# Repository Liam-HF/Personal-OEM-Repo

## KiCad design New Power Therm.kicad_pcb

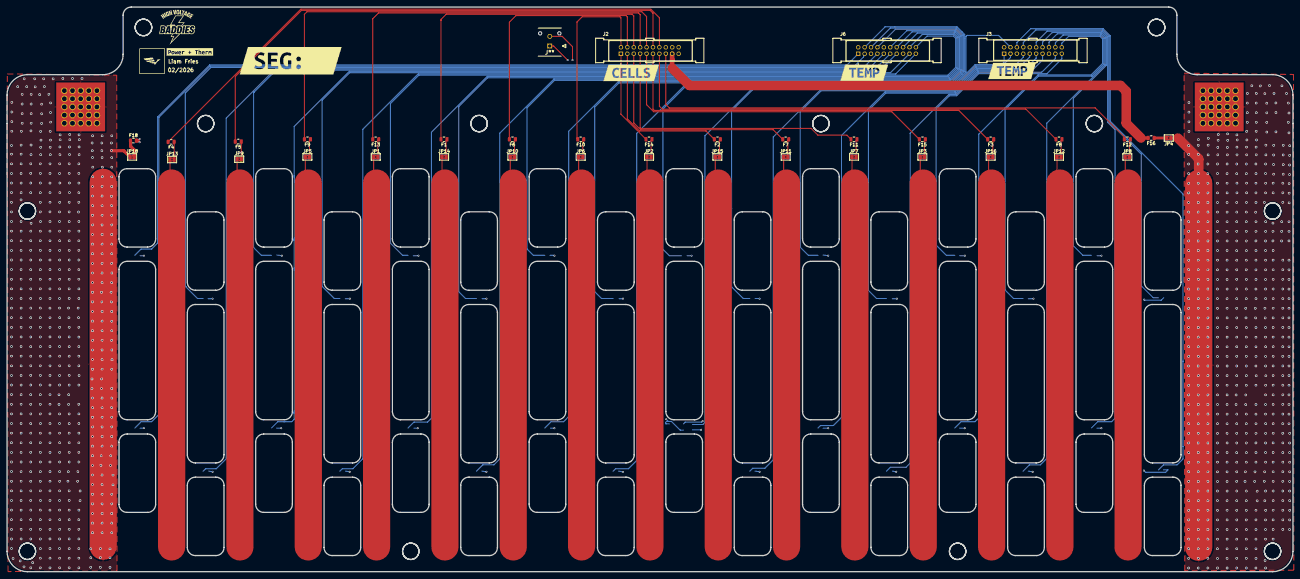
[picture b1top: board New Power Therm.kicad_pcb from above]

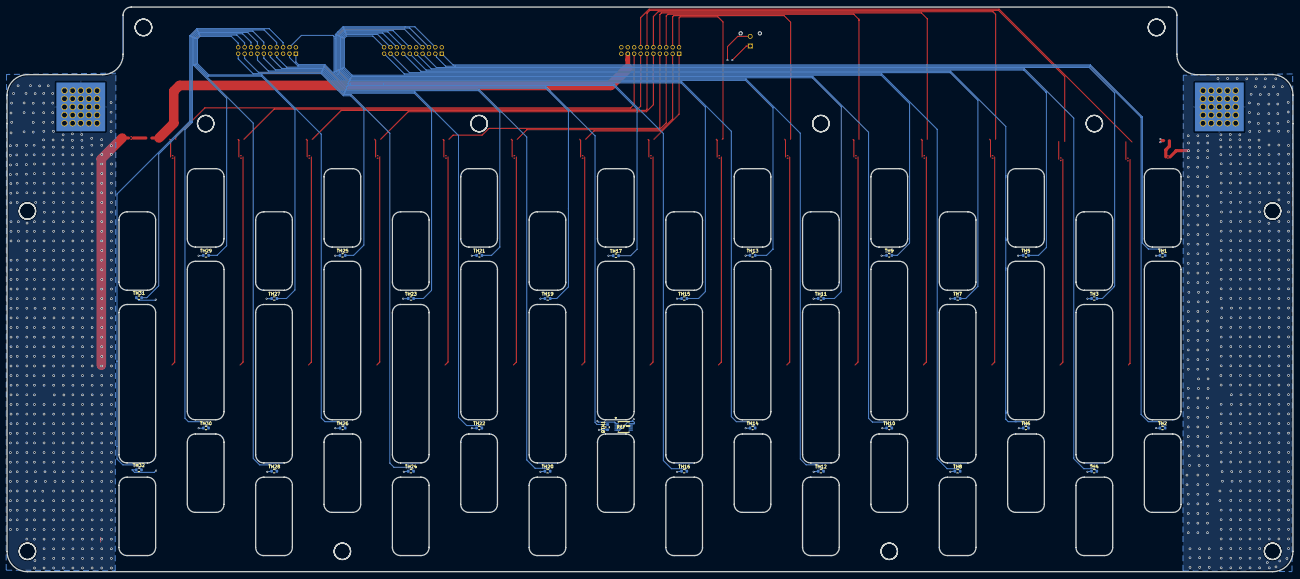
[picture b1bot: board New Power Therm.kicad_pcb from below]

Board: 4 copper layers, 401.0 x 176.1 mm, 92 parts (32 on the bottom side), 66 nets.

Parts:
F1, F2, F3, F4, F5, F6, F7, F8, F9, F10, F11, F12, F13, F14, F15, F16, F18: 200mA_Fuse; Fuse_0805_2012Metric
J2: J_Bond_Pad_4p
J2#2, J3, J6: EHT-110-01-F-D; SAMTEC_EHT-110-01-X-D (J_EHT-110-01-F-D)
J5, J6#2, J7, J8, J9, J10, J11, J12, J13, J14, J15, J16, J17, J18, J19, J20: Battery Cell Spot Weld; J_Bond_Pad_4p
J**: 43045-02YY_121314; J_Molex_Header_01x02_VT - 43045-02YY_121314
JP1, JP2, JP3, JP4, JP5, JP6, JP7, JP8, JP9, JP10, JP11, JP12, JP13, JP14, JP15, JP16, JP18: SolderJumper_2_Bridged; SolderJumper-2_P1.3mm_Bridged2Bar_Pad1.0x1.5mm
TH1, TH2, TH3, TH4, TH5, TH6, TH7, TH8, TH9, TH10, TH11, TH12, TH13, TH14, TH15, TH16, TH17, TH18, TH19, TH20, TH21, TH22, TH23, TH24, TH25, TH26, TH27, TH28, TH29, TH30, TH31, TH32: Thermistor; R_0603_1608Metric
kibuzzard-6738FA22: G***; kibuzzard-6738FA22
kibuzzard-6738FB72, kibuzzard-6738FB72#2: G***; kibuzzard-6738FB72
kibuzzard-6739182D: G***; kibuzzard-6739182D
kibuzzard-67390047: G***; kibuzzard-67390047

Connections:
/Cells[1:16]/CELL0: J20.1, JP18.1 (A)
CELL1: F4.2, J2#2.14, J5.1, JP13.1 (A)
CELL2: F5.2, J2#2.12, J6#2.1, JP9.1 (A)
CELL3: F9.2, J2#2.10, J8.1, JP5.1 (A)
CELL4: F13.2, J2#2.08, J9.1, JP1.1 (A)
CELL5: F1.2, J2#2.06, J10.1, JP14.1 (A)
CELL6: F6.2, J2#2.04, J11.1, JP10.1 (A)
CELL7: F10.2, J2#2.02, J12.1, JP6.1 (A)
CELL8: F14.2, J2#2.01, J13.1, JP2.1 (A)
CELL9: F2.2, J2#2.03, J14.1, JP15.1 (A)
CELL10: F7.2, J2#2.05, J15.1, JP11.1 (A)
CELL11: F11.2, J2#2.07, J16.1, JP7.1 (A)
CELL12: F15.2, J2#2.09, J17.1, JP3.1 (A)
CELL13: F3.2, J2#2.11, J18.1, JP16.1 (A)
CELL14: F8.2, J2#2.13, J19.1, JP12.1 (A)
CELL15: F12.2, J2#2.15, J7.1, JP8.1 (A)
CELL16: F16.2, J2.1, J2#2.17, JP4.1 (A)
GND: F18.2, J2#2.16, J2#2.18, J2#2.19, J2#2.20, J3.05, J3.10, J3.15, J6.05, J6.10, J6.15, TH1.1, TH2.1, TH3.1, TH4.1, TH5.1, TH6.1, TH7.1, TH8.1, TH9.1, TH10.1, TH11.1, TH12.1, TH13.1, TH14.1, TH15.1, TH16.1, TH17.1, TH18.1, TH19.1, TH20.1, TH21.1, TH22.1, TH23.1, TH24.1, TH25.1, TH26.1, TH27.1, TH28.1, TH29.1, TH30.1, TH31.1, TH32.1
unnamed: F5.1, F13.1, JP1.2 (B), JP9.2 (B)
unnamed: F14.1, JP2.2 (B)
unnamed: F15.1, JP3.2 (B)
unnamed: F16.1, JP4.2 (B)
unnamed: F9.1, JP5.2 (B)
unnamed: F10.1, JP6.2 (B)
unnamed: F11.1, JP7.2 (B)
unnamed: F12.1, JP8.2 (B)
unnamed: F6.1, JP10.2 (B)
unnamed: F7.1, JP11.2 (B)
unnamed: F8.1, JP12.2 (B)
unnamed: F4.1, JP13.2 (B)
unnamed: F1.1, JP14.2 (B)
unnamed: F2.1, JP15.2 (B)
unnamed: F3.1, JP16.2 (B)
unnamed: F18.1, JP18.2 (B)
Therm1: J6.01, TH1.2
Therm2: J6.03, TH2.2
Therm3: J6.07, TH3.2
Therm4: J6.09, TH4.2
Therm5: J6.11, TH5.2
Therm6: J6.13, TH6.2
Therm7: J6.17, TH7.2
Therm8: J6.19, TH8.2
Therm9: J6.20, TH9.2
Therm10: J6.18, TH10.2
Therm11: J6.16, TH11.2
Therm12: J6.14, TH12.2
Therm13: J6.12, TH13.2
Therm14: J6.08, TH14.2
Therm15: J6.06, TH15.2
Therm16: J6.04, TH16.2
Therm17: J3.04, TH17.2
Therm18: J3.01, TH18.2
Therm19: J3.03, TH19.2
Therm20: J3.07, TH20.2
Therm21: J3.09, TH21.2
Therm22: J3.11, TH22.2
Therm23: J3.13, TH23.2
Therm24: J3.17, TH24.2
Therm25: J3.19, TH25.2
Therm26: J3.20, TH26.2
Therm27: J3.18, TH27.2
Therm28: J3.16, TH28.2
Therm29: J3.14, TH29.2
Therm30: J3.12, TH30.2
Therm31: J3.08, TH31.2
Therm32: J3.06, TH32.2
